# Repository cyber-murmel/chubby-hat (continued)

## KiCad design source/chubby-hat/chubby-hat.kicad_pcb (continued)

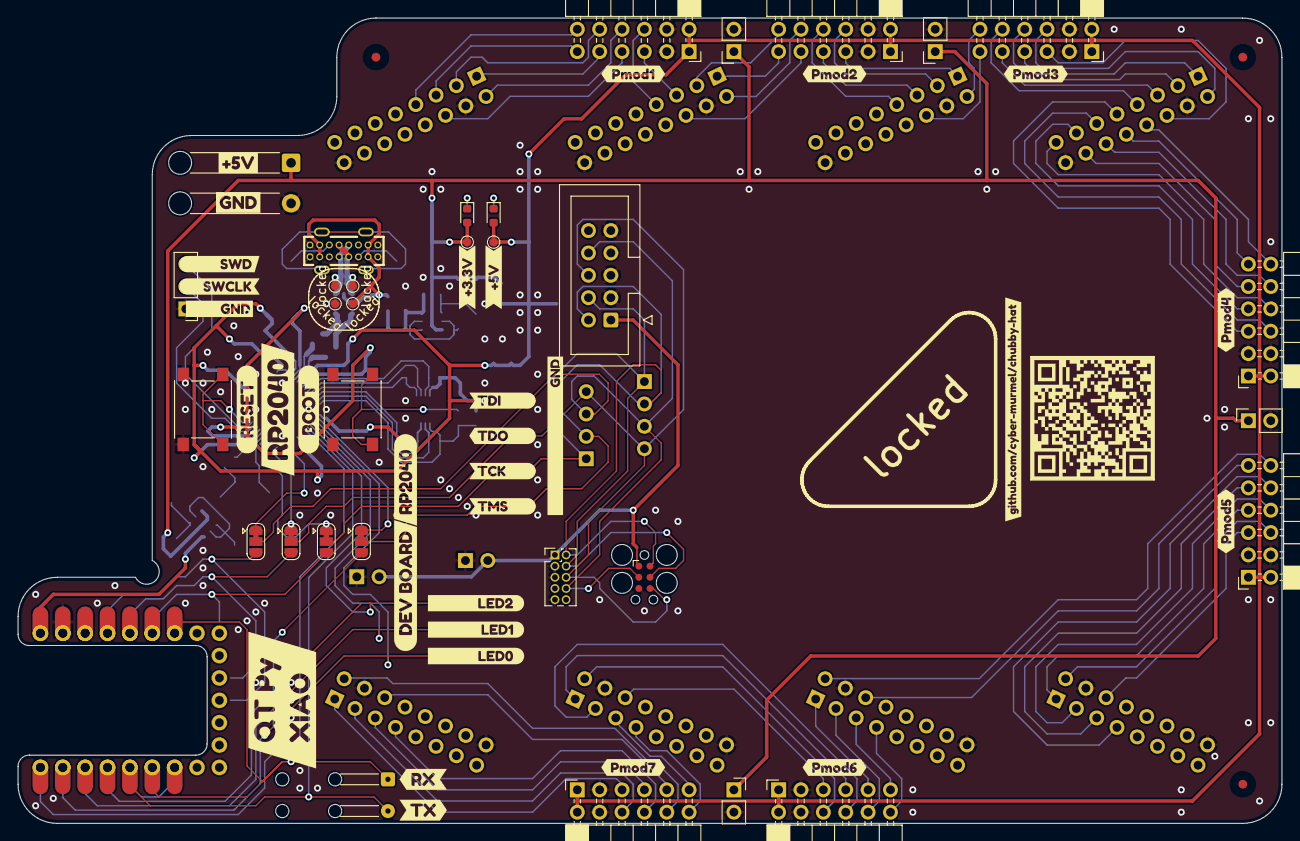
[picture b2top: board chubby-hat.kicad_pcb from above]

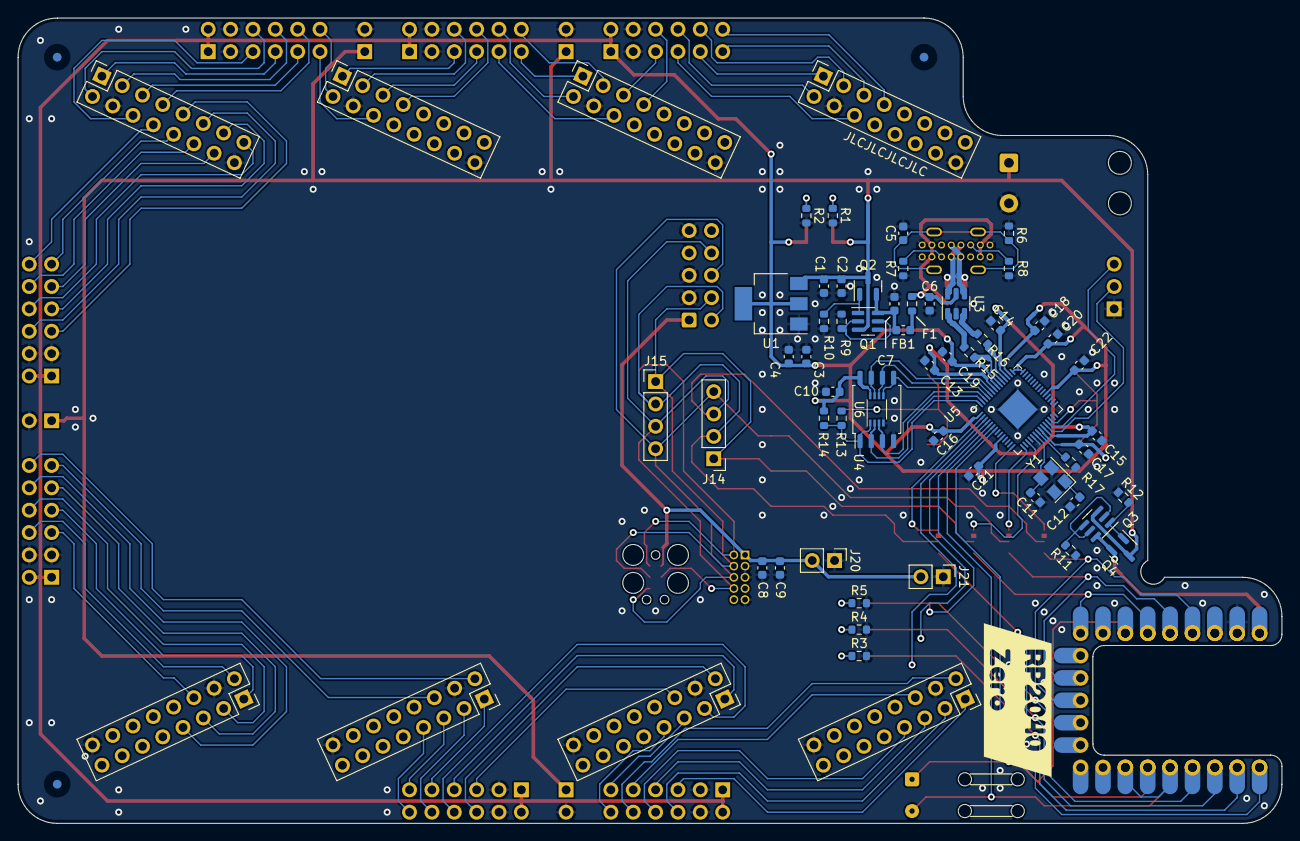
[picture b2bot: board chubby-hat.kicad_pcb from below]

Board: 2 copper layers, 143.5 x 91.4 mm, 143 parts (67 on the bottom side), 115 nets.

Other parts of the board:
QR*****: github.com/cyber-murmel/chubby-hat; github.com_cyber-murmel_chubby-hat
kibuzzard-63D6B6FA: G***; kibuzzard-63D6B6FA
kibuzzard-63D6B15C: G***; kibuzzard-63D6B15C
kibuzzard-63D6B25C: G***; kibuzzard-63D6B25C
kibuzzard-63D6B78A: G***; kibuzzard-63D6B78A
kibuzzard-63D6B79B: G***; kibuzzard-63D6B79B
kibuzzard-63D6B152: G***; kibuzzard-63D6B152
kibuzzard-63D6B171: G***; kibuzzard-63D6B171
kibuzzard-63D6B260: G***; kibuzzard-63D6B260
kibuzzard-63D6CBA0: G***; kibuzzard-63D6CBA0
kibuzzard-63D6CBB9: G***; kibuzzard-63D6CBB9
kibuzzard-63E6D9D7: G***; kibuzzard-63E6D9D7
kibuzzard-63E6D9E4: G***; kibuzzard-63E6D9E4
kibuzzard-63E6D9E9: G***; kibuzzard-63E6D9E9
kibuzzard-63E586AA: G***; kibuzzard-63E586AA
kibuzzard-63E586B9: G***; kibuzzard-63E586B9
kibuzzard-63E586CE: G***; kibuzzard-63E586CE
kibuzzard-63E586D5: G***; kibuzzard-63E586D5
kibuzzard-63E586DD: G***; kibuzzard-63E586DD
kibuzzard-63E586E8: G***; kibuzzard-63E586E8
kibuzzard-63E586F0: G***; kibuzzard-63E586F0
kibuzzard-63E664A0: G***; kibuzzard-63E664A0
kibuzzard-63E664C7: G***; kibuzzard-63E664C7
kibuzzard-63E664D7: G***; kibuzzard-63E664D7
kibuzzard-63E665A8: G***; kibuzzard-63E665A8
kibuzzard-63E665B7: G***; kibuzzard-63E665B7
kibuzzard-63E5252B: G***; kibuzzard-63E5252B
kibuzzard-63E5830C: G***; kibuzzard-63E5830C
kibuzzard-63E5907B: G***; kibuzzard-63E5907B
kibuzzard-63E58302: G***; kibuzzard-63E58302
kibuzzard-63E58321: G***; kibuzzard-63E58321
kibuzzard-63E66495: G***; kibuzzard-63E66495
kibuzzard-63E67724: G***; kibuzzard-63E67724
locked: JP_{TDO}; SolderJumper-3_P1.3mm_Bridged12_RoundedPad1.0x1.5mm
locked#2: JP_{TMS}; SolderJumper-3_P1.3mm_Bridged12_RoundedPad1.0x1.5mm
locked#3: JP_{TDI}; SolderJumper-3_P1.3mm_Bridged12_RoundedPad1.0x1.5mm
locked#4: JP_{TCK}; SolderJumper-3_P1.3mm_Bridged12_RoundedPad1.0x1.5mm

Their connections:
/JTAG.TCK: locked#4.2 (C); also elsewhere on the board
/JTAG.TDI: locked#3.2 (C); also elsewhere on the board
/JTAG.TDO: locked.2 (C); also elsewhere on the board
/JTAG.TMS: locked#2.2 (C); also elsewhere on the board
/JTAG_{DevBoard}.TCK: locked#4.3 (B); also elsewhere on the board
/JTAG_{DevBoard}.TDI: locked#3.3 (B); also elsewhere on the board
/JTAG_{DevBoard}.TDO: locked.3 (B); also elsewhere on the board
/JTAG_{DevBoard}.TMS: locked#2.3 (B); also elsewhere on the board
/RP2040/GPIO0: locked#2.1 (A); also elsewhere on the board
/RP2040/GPIO11: locked#3.1 (A); also elsewhere on the board
/RP2040/GPIO12: locked.1 (A); also elsewhere on the board
/RP2040/GPIO14: locked#4.1 (A); also elsewhere on the board

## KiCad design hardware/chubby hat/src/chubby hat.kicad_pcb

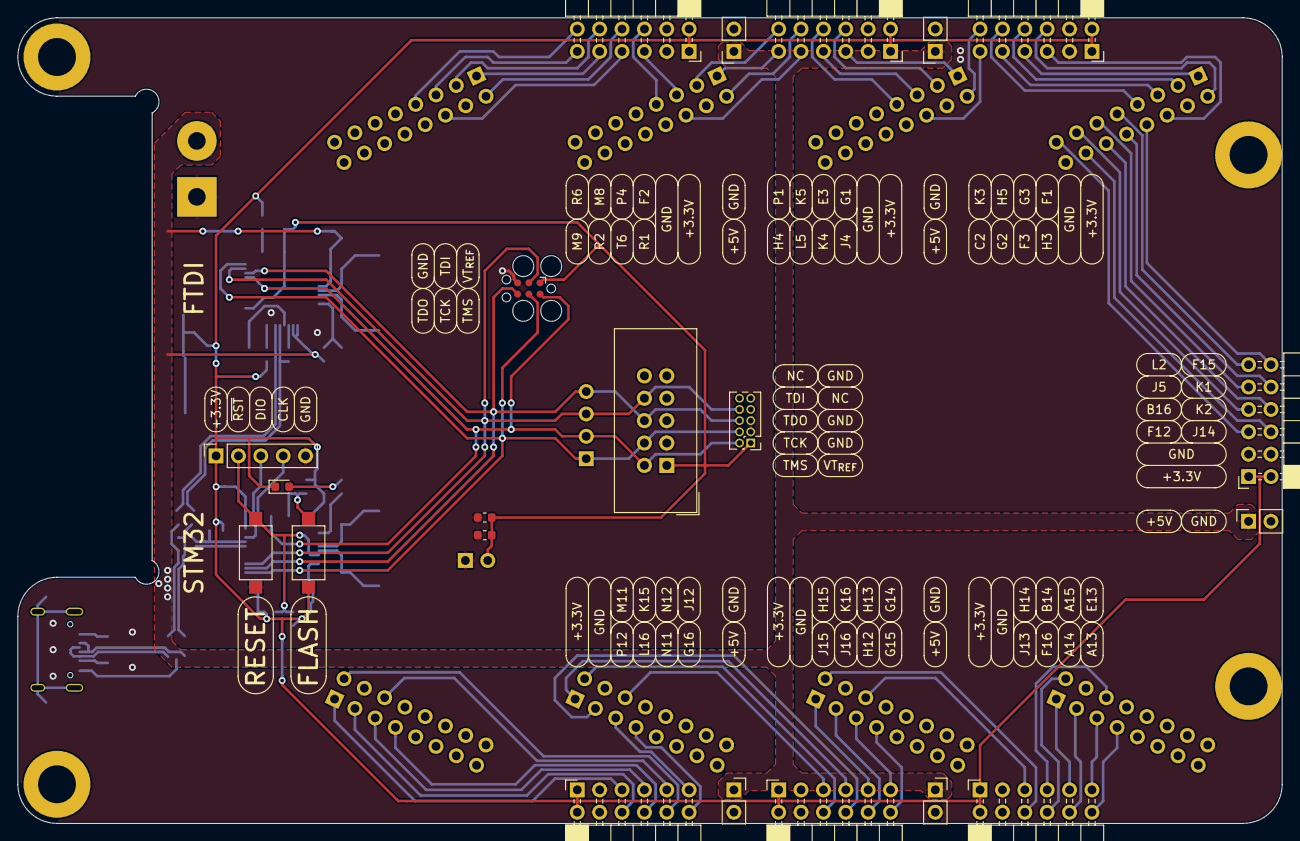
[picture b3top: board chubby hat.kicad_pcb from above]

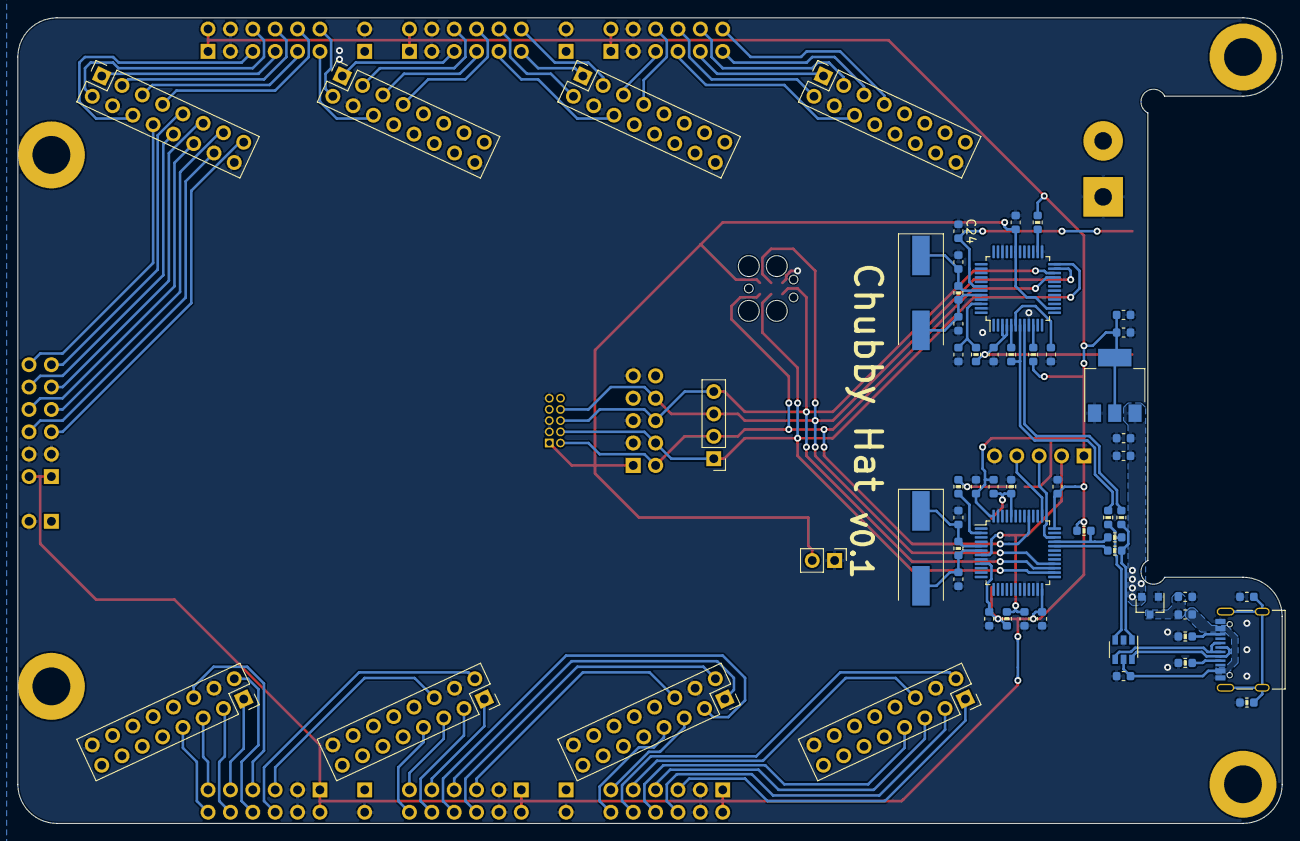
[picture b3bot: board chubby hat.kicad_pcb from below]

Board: 2 copper layers, 143.5 x 91.4 mm, 84 parts (58 on the bottom side), 92 nets.

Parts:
C1, C2, C3, C4, C6, C9, C10, C11, C12, C13, C14, C19, C20, C22, C23, C24: 100n; C_0603_1608Metric_Icon
C5, C7, C8, C21: 1u; C_0603_1608Metric_Icon
C15, C16, C17, C18: 36p; C_0603_1608Metric_Icon
D1: pink; LED_0603_1608Metric
FB1: 600Ω@100MHz; L_0603_1608Metric
H1, H2, H3, H4: M4; MountingHole_4.3mm_M4_ISO7380_Pad
J1, J2, J3, J4, J5, J6, J7, J8: HUB75; PinSocket_2x08_P2.54mm_Vertical
J9: Screw_Terminal_01x02; SolderWirePad_1x02_P7.62mm_Drill2mm
J10: Conn_01x02; PinHeader_1x02_P2.54mm_Vertical
J11: Conn_01x04; PinHeader_1x04_P2.54mm_Vertical
J12: USB_C_Receptacle_USB2.0; USB_C_Receptacle_Palconn_UTC16-G
J13: Conn_ARM_JTAG_SWD_10; IDC-Header_2x05_P2.54mm_Vertical
J14: SWD; PinSocket_1x05_P2.54mm_Vertical
J15, J16, J17, J18, J19: 5V; PinSocket_1x02_P2.54mm_Vertical
J20: Conn_ARM_JTAG_SWD_10; PinHeader_2x05_P1.27mm_Vertical
J21: TC2030; Tag-Connect_TC2030-IDC-FP_2x03_P1.27mm_Vertical
Pmod1, Pmod2, Pmod3, Pmod4, Pmod5, Pmod6, Pmod7: Pmod_02x06_Host; PinSocket_2x06_P2.54mm_Horizontal
Q1: AO3401A; SOT-23
R1, R2: 27; R_0603_1608Metric_Icon
R3, R8, R9: 1M; R_0603_1608Metric_Icon
R6, R7: 20; R_0603_1608Metric_Icon
R10, R11: 5.1k; R_0603_1608Metric_Icon
R12, R16, R19, R20: 1.5k; R_0603_1608Metric_Icon
R13, R15, R17: 10k; R_0603_1608Metric_Icon
R18: 470; R_0603_1608Metric_Icon
SW2: reset; SW_SPST_CK_RS282G05A3
SW3: boot0; SW_SPST_CK_RS282G05A3
U1: FT2232D; LQFP-48_7x7mm_P0.5mm
U2: USBLC6-2SC6; SOT-23-6
U3: STM32F103C8Tx; LQFP-48_7x7mm_P0.5mm
U4: AMS1117-3.3; SOT-223-3_TabPin2
Y1: 6MHz; Crystal_SMD_HC49-SD
Y2: 8MHz; Crystal_SMD_HC49-SD

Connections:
+3V3: C8.2, C9.2, C10.2, C11.2, C12.2, C13.2, C23.1, D1.1 (K), J14.1, Pmod1.1 (VCC), Pmod1.2 (VCC), Pmod2.1 (VCC), Pmod2.2 (VCC), Pmod3.1 (VCC), Pmod3.2 (VCC), Pmod4.1 (VCC), Pmod4.2 (VCC), Pmod5.1 (VCC), Pmod5.2 (VCC), Pmod6.1 (VCC), Pmod6.2 (VCC), Pmod7.1 (VCC), Pmod7.2 (VCC), R12.2, R13.2, R19.1, R20.1, SW3.1, U3.9 (VDDA), U3.24 (VDD), U3.36 (VDD), U3.48 (VDD), U4.2 (VO)
+5V: C6.2, C7.2, C20.2, C24.2, J9.2, J15.1, J16.1, J17.1, J18.1, J19.1, Q1.2 (S), R18.2, U1.3 (VCC), U1.4 (~RESET), U1.42 (VCC), U4.3 (VI)
/Blue Pill/BOOT0: C23.2, R15.1, SW3.2, U3.44 (BOOT0)
/Blue Pill/D_N: R7.2, U3.32 (PA11)
/Blue Pill/D_P: R6.1, R12.1, U3.33 (PA12)
/Blue Pill/OSCIN: C15.2, R3.1, U3.5 (PD0), Y2.1
/Blue Pill/OSCOUT: C16.2, R3.2, U3.6 (PD1), Y2.2
/Blue Pill/STM32_~RESET~: C14.2, J14.2, R13.1, SW2.2, U3.7 (NRST)
/Blue Pill/SWCLK: J14.4, U3.37 (PA14)
/Blue Pill/SWDIO: J14.3, U3.34 (PA13)
/FTDI/D_N: R1.1, U1.8 (USBDM)
/FTDI/D_P: R2.2, R16.2, U1.7 (USBDP)
/JTAG.TCK: J11.1, J13.4 (SWDCLK/TCK), J20.4 (SWDCLK/TCK), J21.4, U1.24 (ADBUS0), U3.26 (PB13)
/JTAG.TDI: J11.3, J13.8 (NC/TDI), J20.8 (NC/TDI), J21.3, U1.23 (ADBUS1), U3.28 (PB15)
/JTAG.TDO: J11.4, J13.6 (SWO/TDO), J20.6 (SWO/TDO), J21.6, U1.22 (ADBUS2), U3.27 (PB14)
/JTAG.TMS: J11.2, J13.2 (SWDIO/TMS), J20.2 (SWDIO/TMS), J21.2, U1.21 (ADBUS3), U3.40 (PB4)
/Pmod1_IO1: J1.9, Pmod1.11 (IO1)
/Pmod1_IO2: J1.11, Pmod1.9 (IO2)
/Pmod1_IO3: J1.13, Pmod1.7 (IO3)
/Pmod1_IO4: J1.15, Pmod1.5 (IO4)
/Pmod1_IO5: J1.8, Pmod1.12 (IO5)
/Pmod1_IO6: J1.10, Pmod1.10 (IO6)
/Pmod1_IO7: J1.12, Pmod1.8 (IO7)
/Pmod1_IO8: J1.14, Pmod1.6 (IO8)
/Pmod2_IO1: J2.6, Pmod2.11 (IO1)
/Pmod2_IO2: J1.5, Pmod2.9 (IO2)
/Pmod2_IO3: J1.1, Pmod2.7 (IO3)
/Pmod2_IO4: J1.6, Pmod2.5 (IO4)
/Pmod2_IO5: J2.2, Pmod2.12 (IO5)
/Pmod2_IO6: J1.7, Pmod2.10 (IO6)
/Pmod2_IO7: J1.3, Pmod2.8 (IO7)
/Pmod2_IO8: J1.2, Pmod2.6 (IO8)
/Pmod3_IO1: J3.1, Pmod3.11 (IO1)
/Pmod3_IO2: J3.6, Pmod3.9 (IO2)
/Pmod3_IO3: J2.5, Pmod3.7 (IO3)
/Pmod3_IO4: J2.1, Pmod3.5 (IO4)
/Pmod3_IO5: J3.3, Pmod3.12 (IO5)
/Pmod3_IO6: J3.2, Pmod3.10 (IO6)
/Pmod3_IO7: J2.7, Pmod3.8 (IO7)
/Pmod3_IO8: J2.3, Pmod3.6 (IO8)
/Pmod4_IO1: J4.5, Pmod4.11 (IO1)
/Pmod4_IO2: J4.1, Pmod4.9 (IO2)
/Pmod4_IO3: J4.6, Pmod4.7 (IO3)
/Pmod4_IO4: J3.5, Pmod4.5 (IO4)
/Pmod4_IO5: J4.7, Pmod4.12 (IO5)
/Pmod4_IO6: J4.3, Pmod4.10 (IO6)
/Pmod4_IO7: J4.2, Pmod4.8 (IO7)
/Pmod4_IO8: J3.7, Pmod4.6 (IO8)
/Pmod5_IO1: J6.5, Pmod5.11 (IO1)
/Pmod5_IO2: J5.6, Pmod5.9 (IO2)
/Pmod5_IO3: J5.5, Pmod5.7 (IO3)
/Pmod5_IO4: J5.1, Pmod5.5 (IO4)
/Pmod5_IO5: J6.7, Pmod5.12 (IO5)
/Pmod5_IO6: J5.2, Pmod5.10 (IO6)
/Pmod5_IO7: J5.7, Pmod5.8 (IO7)
/Pmod5_IO8: J5.3, Pmod5.6 (IO8)
/Pmod6_IO1: J7.5, Pmod6.11 (IO1)
/Pmod6_IO2: J7.1, Pmod6.9 (IO2)
/Pmod6_IO3: J6.1, Pmod6.7 (IO3)
/Pmod6_IO4: J6.6, Pmod6.5 (IO4)
/Pmod6_IO5: J7.7, Pmod6.12 (IO5)
/Pmod6_IO6: J7.3, Pmod6.10 (IO6)
/Pmod6_IO7: J6.3, Pmod6.8 (IO7)
/Pmod6_IO8: J6.2, Pmod6.6 (IO8)
/Pmod7_IO1: J8.5, Pmod7.11 (IO1)
/Pmod7_IO2: J8.1, Pmod7.9 (IO2)
/Pmod7_IO3: J8.6, Pmod7.7 (IO3)
/Pmod7_IO4: J7.6, Pmod7.5 (IO4)
/Pmod7_IO5: J8.7, Pmod7.12 (IO5)
/Pmod7_IO6: J8.3, Pmod7.10 (IO6)
/Pmod7_IO7: J8.2, Pmod7.8 (IO7)
/Pmod7_IO8: J7.2, Pmod7.6 (IO8)
/Type C USB 2.0/D_N: J12.A7 (D-), J12.B7 (D-), U2.6 (IO1)
/Type C USB 2.0/D_P: J12.A6 (D+), J12.B6 (D+), U2.4 (IO2)
/USB.D+: R2.1, R6.2, U2.3 (IO2)
/USB.D-: R1.2, R7.1, U2.1 (IO1)
Earth: C3.1, J12.S1 (SHIELD), R9.2
GND: C1.2, C2.2, C3.2, C4.1, C5.1, C6.1, C7.1, C8.1, C9.1, C10.1, C11.1, C12.1, C13.1, C14.1, C15.1, C16.1, C17.1, C18.1, C19.1, C20.1, C21.1, C22.1, C24.1, J1.4, J1.16, J2.4, J2.16, J3.4, J3.16, J4.4, J4.16, J5.4, J5.16, J6.4, J6.16, J7.4, J7.16, J8.4, J8.16, J9.1, J10.1, J12.A1 (GND), J12.A12 (GND), J12.B1 (GND), J12.B12 (GND), J13.3 (GND), J13.5 (GND), J13.9 (GNDDetect), J14.5, J15.2, J16.2, J17.2, J18.2, J19.2, J20.3 (GND), J20.5 (GND), J20.9 (GNDDetect), J21.5, Pmod1.3 (GND), Pmod1.4 (GND), Pmod2.3 (GND), Pmod2.4 (GND), Pmod3.3 (GND), Pmod3.4 (GND), Pmod4.3 (GND), Pmod4.4 (GND), Pmod5.3 (GND), Pmod5.4 (GND), Pmod6.3 (GND), Pmod6.4 (GND), Pmod7.3 (GND), Pmod7.4 (GND), Q1.1 (G), R9.1, R10.1, R11.1, R15.2, SW2.1, U1.9 (GND), U1.18 (GND), U1.25 (GND), U1.34 (GND), U1.45 (AGND), U1.47 (TEST), U2.2 (GND), U3.8 (VSSA), U3.20 (PB2), U3.23 (VSS), U3.35 (VSS), U3.47 (VSS), U4.1 (GND)
unnamed: C2.1, U1.6 (3V3OUT)
unnamed: C5.2, FB1.1, Q1.3 (D)
unnamed: C17.2, R8.1, U1.43 (XTIN), Y1.1
unnamed: C18.2, R8.2, U1.44 (XTOUT), Y1.2
unnamed: C19.2, R18.1, U1.46 (AVCC)
unnamed: D1.2 (A), R17.2
unnamed: J12.A5 (CC1), R10.2
unnamed: J12.B5 (CC2), R11.2
unnamed: R16.1, U1.5 (~RSTOUT)
unnamed: R17.1, U3.2 (PC13)
unnamed: R19.2, U1.10 (SI/WUA)
unnamed: R20.2, U1.26 (SI/WUB)
VBUS: C4.2, FB1.2, J12.A4 (VBUS), J12.A9 (VBUS), J12.B4 (VBUS), J12.B9 (VBUS), U2.5 (VBUS)
VDD: C1.1, C21.2, C22.2, J10.2, J13.1 (VTref), J20.1 (VTref), J21.1, U1.14 (VCCIOA), U1.31 (VCCIOB)

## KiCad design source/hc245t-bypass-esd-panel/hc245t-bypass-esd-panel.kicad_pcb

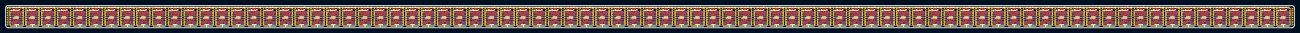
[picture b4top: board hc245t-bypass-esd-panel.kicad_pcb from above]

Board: 2 copper layers, 466.0 x 8.0 mm, 405 parts (0 on the bottom side), 11 nets.

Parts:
C1, C2, C3, C4, C5, C6, C7, C8, C9, C10, C11, C12, C13, C14, C15, C16, C17, C18, C19, C20, C21, C22, C23, C24, C25, C26, C27, C28, C29, C30, C31, C32, C33, C34, C35, C36, C37, C38, C39, C40, C41, C42, C43, C44, C45, C46, C47, C48, C49, C50, C51, C52, C53, C54, C55, C56, C57, C58, C59, C60, C61, C62, C63, C64, C65, C66, C67, C68, C69, C70, C71, C72, C73, C74, C75, C76, C77, C78, C79, C80, C81: C; C_0402_1005Metric
R1, R2, R3, R4, R5, R6, R7, R8, R9, R10, R11, R12, R13, R14, R15, R16, R17, R18, R19, R20, R21, R22, R23, R24, R25, R26, R27, R28, R29, R30, R31, R32, R33, R34, R35, R36, R37, R38, R39, R40, R41, R42, R43, R44, R45, R46, R47, R48, R49, R50, R51, R52, R53, R54, R55, R56, R57, R58, R59, R60, R61, R62, R63, R64, R65, R66, R67, R68, R69, R70, R71, R72, R73, R74, R75, R76, R77, R78, R79, R80, R81: R; R_0402_1005Metric
U1, U4, U7, U10, U13, U16, U19, U22, U25, U28, U31, U34, U37, U40, U43, U46, U49, U52, U55, U58, U61, U64, U67, U70, U73, U76, U79, U82, U85, U88, U91, U94, U97, U100, U103, U106, U109, U112, U115, U118, U121, U124, U127, U130, U133, U136, U139, U142, U145, U148, U151, U154, U157, U160, U163, U166, U169, U172, U175, U178, U181, U184, U187, U190, U193, U196, U199, U202, U205, U208, U211, U214, U217, U220, U223, U226, U229, U232, U235, U238, U241: 74HC245; TSSOP-20_4.4x6.5mm_P0.65mm
U2, U3, U5, U6, U8, U9, U11, U12, U14, U15, U17, U18, U20, U21, U23, U24, U26, U27, U29, U30, U32, U33, U35, U36, U38, U39, U41, U42, U44, U45, U47, U48, U50, U51, U53, U54, U56, U57, U59, U60, U62, U63, U65, U66, U68, U69, U71, U72, U74, U75, U77, U78, U80, U81, U83, U84, U86, U87, U89, U90, U92, U93, U95, U96, U98, U99, U101, U102, U104, U105, U107, U108, U110, U111, U113, U114, U116, U117, U119, U120, U122, U123, U125, U126, U128, U129, U131, U132, U134, U135, U137, U138, U140, U141, U143, U144, U146, U147, U149, U150, U152, U153, U155, U156, U158, U159, U161, U162, U164, U165, U167, U168, U170, U171, U173, U174, U176, U177, U179, U180, U182, U183, U185, U186, U188, U189, U191, U192, U194, U195, U197, U198, U200, U201, U203, U204, U206, U207, U209, U210, U212, U213, U215, U216, U218, U219, U221, U222, U224, U225, U227, U228, U230, U231, U233, U234, U236, U237, U239, U240, U242, U243: NUP4202; SOT-363_SC-70-6

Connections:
/D0: U1.2 (A0), U1.18 (B0), U2.6, U4.2 (A0), U4.18 (B0), U5.6, U7.2 (A0), U7.18 (B0), U8.6, U10.2 (A0), U10.18 (B0), U11.6, U13.2 (A0), U13.18 (B0), U14.6, U16.2 (A0), U16.18 (B0), U17.6, U19.2 (A0), U19.18 (B0), U20.6, U22.2 (A0), U22.18 (B0), U23.6, U25.2 (A0), U25.18 (B0), U26.6, U28.2 (A0), U28.18 (B0), U29.6, U31.2 (A0), U31.18 (B0), U32.6, U34.2 (A0), U34.18 (B0), U35.6, U37.2 (A0), U37.18 (B0), U38.6, U40.2 (A0), U40.18 (B0), U41.6, U43.2 (A0), U43.18 (B0), U44.6, U46.2 (A0), U46.18 (B0), U47.6, U49.2 (A0), U49.18 (B0), U50.6, U52.2 (A0), U52.18 (B0), U53.6, U55.2 (A0), U55.18 (B0), U56.6, U58.2 (A0), U58.18 (B0), U59.6, U61.2 (A0), U61.18 (B0), U62.6, U64.2 (A0), U64.18 (B0), U65.6, U67.2 (A0), U67.18 (B0), U68.6, U70.2 (A0), U70.18 (B0), U71.6, U73.2 (A0), U73.18 (B0), U74.6, U76.2 (A0), U76.18 (B0), U77.6, U79.2 (A0), U79.18 (B0), U80.6, U82.2 (A0), U82.18 (B0), U83.6, U85.2 (A0), U85.18 (B0), U86.6, U88.2 (A0), U88.18 (B0), U89.6, U91.2 (A0), U91.18 (B0), U92.6, U94.2 (A0), U94.18 (B0), U95.6, U97.2 (A0), U97.18 (B0), U98.6, U100.2 (A0), U100.18 (B0), U101.6, U103.2 (A0), U103.18 (B0), U104.6, U106.2 (A0), U106.18 (B0), U107.6, U109.2 (A0), U109.18 (B0), U110.6, U112.2 (A0), U112.18 (B0), U113.6, U115.2 (A0), U115.18 (B0), U116.6, U118.2 (A0), U118.18 (B0), U119.6, U121.2 (A0), U121.18 (B0), U122.6, U124.2 (A0), U124.18 (B0), U125.6, U127.2 (A0), U127.18 (B0), U128.6, U130.2 (A0), U130.18 (B0), U131.6, U133.2 (A0), U133.18 (B0), U134.6, U136.2 (A0), U136.18 (B0), U137.6, U139.2 (A0), U139.18 (B0), U140.6, U142.2 (A0), U142.18 (B0), U143.6, U145.2 (A0), U145.18 (B0), U146.6, U148.2 (A0), U148.18 (B0), U149.6, U151.2 (A0), U151.18 (B0), U152.6, U154.2 (A0), U154.18 (B0), U155.6, U157.2 (A0), U157.18 (B0), U158.6, U160.2 (A0), U160.18 (B0), U161.6, U163.2 (A0), U163.18 (B0), U164.6, U166.2 (A0), U166.18 (B0), U167.6, U169.2 (A0), U169.18 (B0), U170.6, U172.2 (A0), U172.18 (B0), U173.6, U175.2 (A0), U175.18 (B0), U176.6, U178.2 (A0), U178.18 (B0), U179.6, U181.2 (A0), U181.18 (B0), U182.6, U184.2 (A0), U184.18 (B0), U185.6, U187.2 (A0), U187.18 (B0), U188.6, U190.2 (A0)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
/D1: U1.3 (A1), U1.17 (B1), U2.1, U4.3 (A1), U4.17 (B1), U5.1, U7.3 (A1), U7.17 (B1), U8.1, U10.3 (A1), U10.17 (B1), U11.1, U13.3 (A1), U13.17 (B1), U14.1, U16.3 (A1), U16.17 (B1), U17.1, U19.3 (A1), U19.17 (B1), U20.1, U22.3 (A1), U22.17 (B1), U23.1, U25.3 (A1), U25.17 (B1), U26.1, U28.3 (A1), U28.17 (B1), U29.1, U31.3 (A1), U31.17 (B1), U32.1, U34.3 (A1), U34.17 (B1), U35.1, U37.3 (A1), U37.17 (B1), U38.1, U40.3 (A1), U40.17 (B1), U41.1, U43.3 (A1), U43.17 (B1), U44.1, U46.3 (A1), U46.17 (B1), U47.1, U49.3 (A1), U49.17 (B1), U50.1, U52.3 (A1), U52.17 (B1), U53.1, U55.3 (A1), U55.17 (B1), U56.1, U58.3 (A1), U58.17 (B1), U59.1, U61.3 (A1), U61.17 (B1), U62.1, U64.3 (A1), U64.17 (B1), U65.1, U67.3 (A1), U67.17 (B1), U68.1, U70.3 (A1), U70.17 (B1), U71.1, U73.3 (A1), U73.17 (B1), U74.1, U76.3 (A1), U76.17 (B1), U77.1, U79.3 (A1), U79.17 (B1), U80.1, U82.3 (A1), U82.17 (B1), U83.1, U85.3 (A1), U85.17 (B1), U86.1, U88.3 (A1), U88.17 (B1), U89.1, U91.3 (A1), U91.17 (B1), U92.1, U94.3 (A1), U94.17 (B1), U95.1, U97.3 (A1), U97.17 (B1), U98.1, U100.3 (A1), U100.17 (B1), U101.1, U103.3 (A1), U103.17 (B1), U104.1, U106.3 (A1), U106.17 (B1), U107.1, U109.3 (A1), U109.17 (B1), U110.1, U112.3 (A1), U112.17 (B1), U113.1, U115.3 (A1), U115.17 (B1), U116.1, U118.3 (A1), U118.17 (B1), U119.1, U121.3 (A1), U121.17 (B1), U122.1, U124.3 (A1), U124.17 (B1), U125.1, U127.3 (A1), U127.17 (B1), U128.1, U130.3 (A1), U130.17 (B1), U131.1, U133.3 (A1), U133.17 (B1), U134.1, U136.3 (A1), U136.17 (B1), U137.1, U139.3 (A1), U139.17 (B1), U140.1, U142.3 (A1), U142.17 (B1), U143.1, U145.3 (A1), U145.17 (B1), U146.1, U148.3 (A1), U148.17 (B1), U149.1, U151.3 (A1), U151.17 (B1), U152.1, U154.3 (A1), U154.17 (B1), U155.1, U157.3 (A1), U157.17 (B1), U158.1, U160.3 (A1), U160.17 (B1), U161.1, U163.3 (A1), U163.17 (B1), U164.1, U166.3 (A1), U166.17 (B1), U167.1, U169.3 (A1), U169.17 (B1), U170.1, U172.3 (A1), U172.17 (B1), U173.1, U175.3 (A1), U175.17 (B1), U176.1, U178.3 (A1), U178.17 (B1), U179.1, U181.3 (A1), U181.17 (B1), U182.1, U184.3 (A1), U184.17 (B1), U185.1, U187.3 (A1), U187.17 (B1), U188.1, U190.3 (A1)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
/D2: U1.4 (A2), U1.16 (B2), U2.4, U4.4 (A2), U4.16 (B2), U5.4, U7.4 (A2), U7.16 (B2), U8.4, U10.4 (A2), U10.16 (B2), U11.4, U13.4 (A2), U13.16 (B2), U14.4, U16.4 (A2), U16.16 (B2), U17.4, U19.4 (A2), U19.16 (B2), U20.4, U22.4 (A2), U22.16 (B2), U23.4, U25.4 (A2), U25.16 (B2), U26.4, U28.4 (A2), U28.16 (B2), U29.4, U31.4 (A2), U31.16 (B2), U32.4, U34.4 (A2), U34.16 (B2), U35.4, U37.4 (A2), U37.16 (B2), U38.4, U40.4 (A2), U40.16 (B2), U41.4, U43.4 (A2), U43.16 (B2), U44.4, U46.4 (A2), U46.16 (B2), U47.4, U49.4 (A2), U49.16 (B2), U50.4, U52.4 (A2), U52.16 (B2), U53.4, U55.4 (A2), U55.16 (B2), U56.4, U58.4 (A2), U58.16 (B2), U59.4, U61.4 (A2), U61.16 (B2), U62.4, U64.4 (A2), U64.16 (B2), U65.4, U67.4 (A2), U67.16 (B2), U68.4, U70.4 (A2), U70.16 (B2), U71.4, U73.4 (A2), U73.16 (B2), U74.4, U76.4 (A2), U76.16 (B2), U77.4, U79.4 (A2), U79.16 (B2), U80.4, U82.4 (A2), U82.16 (B2), U83.4, U85.4 (A2), U85.16 (B2), U86.4, U88.4 (A2), U88.16 (B2), U89.4, U91.4 (A2), U91.16 (B2), U92.4, U94.4 (A2), U94.16 (B2), U95.4, U97.4 (A2), U97.16 (B2), U98.4, U100.4 (A2), U100.16 (B2), U101.4, U103.4 (A2), U103.16 (B2), U104.4, U106.4 (A2), U106.16 (B2), U107.4, U109.4 (A2), U109.16 (B2), U110.4, U112.4 (A2), U112.16 (B2), U113.4, U115.4 (A2), U115.16 (B2), U116.4, U118.4 (A2), U118.16 (B2), U119.4, U121.4 (A2), U121.16 (B2), U122.4, U124.4 (A2), U124.16 (B2), U125.4, U127.4 (A2), U127.16 (B2), U128.4, U130.4 (A2), U130.16 (B2), U131.4, U133.4 (A2), U133.16 (B2), U134.4, U136.4 (A2), U136.16 (B2), U137.4, U139.4 (A2), U139.16 (B2), U140.4, U142.4 (A2), U142.16 (B2), U143.4, U145.4 (A2), U145.16 (B2), U146.4, U148.4 (A2), U148.16 (B2), U149.4, U151.4 (A2), U151.16 (B2), U152.4, U154.4 (A2), U154.16 (B2), U155.4, U157.4 (A2), U157.16 (B2), U158.4, U160.4 (A2), U160.16 (B2), U161.4, U163.4 (A2), U163.16 (B2), U164.4, U166.4 (A2), U166.16 (B2), U167.4, U169.4 (A2), U169.16 (B2), U170.4, U172.4 (A2), U172.16 (B2), U173.4, U175.4 (A2), U175.16 (B2), U176.4, U178.4 (A2), U178.16 (B2), U179.4, U181.4 (A2), U181.16 (B2), U182.4, U184.4 (A2), U184.16 (B2), U185.4, U187.4 (A2), U187.16 (B2), U188.4, U190.4 (A2)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
/D3: U1.5 (A3), U1.15 (B3), U2.3, U4.5 (A3), U4.15 (B3), U5.3, U7.5 (A3), U7.15 (B3), U8.3, U10.5 (A3), U10.15 (B3), U11.3, U13.5 (A3), U13.15 (B3), U14.3, U16.5 (A3), U16.15 (B3), U17.3, U19.5 (A3), U19.15 (B3), U20.3, U22.5 (A3), U22.15 (B3), U23.3, U25.5 (A3), U25.15 (B3), U26.3, U28.5 (A3), U28.15 (B3), U29.3, U31.5 (A3), U31.15 (B3), U32.3, U34.5 (A3), U34.15 (B3), U35.3, U37.5 (A3), U37.15 (B3), U38.3, U40.5 (A3), U40.15 (B3), U41.3, U43.5 (A3), U43.15 (B3), U44.3, U46.5 (A3), U46.15 (B3), U47.3, U49.5 (A3), U49.15 (B3), U50.3, U52.5 (A3), U52.15 (B3), U53.3, U55.5 (A3), U55.15 (B3), U56.3, U58.5 (A3), U58.15 (B3), U59.3, U61.5 (A3), U61.15 (B3), U62.3, U64.5 (A3), U64.15 (B3), U65.3, U67.5 (A3), U67.15 (B3), U68.3, U70.5 (A3), U70.15 (B3), U71.3, U73.5 (A3), U73.15 (B3), U74.3, U76.5 (A3), U76.15 (B3), U77.3, U79.5 (A3), U79.15 (B3), U80.3, U82.5 (A3), U82.15 (B3), U83.3, U85.5 (A3), U85.15 (B3), U86.3, U88.5 (A3), U88.15 (B3), U89.3, U91.5 (A3), U91.15 (B3), U92.3, U94.5 (A3), U94.15 (B3), U95.3, U97.5 (A3), U97.15 (B3), U98.3, U100.5 (A3), U100.15 (B3), U101.3, U103.5 (A3), U103.15 (B3), U104.3, U106.5 (A3), U106.15 (B3), U107.3, U109.5 (A3), U109.15 (B3), U110.3, U112.5 (A3), U112.15 (B3), U113.3, U115.5 (A3), U115.15 (B3), U116.3, U118.5 (A3), U118.15 (B3), U119.3, U121.5 (A3), U121.15 (B3), U122.3, U124.5 (A3), U124.15 (B3), U125.3, U127.5 (A3), U127.15 (B3), U128.3, U130.5 (A3), U130.15 (B3), U131.3, U133.5 (A3), U133.15 (B3), U134.3, U136.5 (A3), U136.15 (B3), U137.3, U139.5 (A3), U139.15 (B3), U140.3, U142.5 (A3), U142.15 (B3), U143.3, U145.5 (A3), U145.15 (B3), U146.3, U148.5 (A3), U148.15 (B3), U149.3, U151.5 (A3), U151.15 (B3), U152.3, U154.5 (A3), U154.15 (B3), U155.3, U157.5 (A3), U157.15 (B3), U158.3, U160.5 (A3), U160.15 (B3), U161.3, U163.5 (A3), U163.15 (B3), U164.3, U166.5 (A3), U166.15 (B3), U167.3, U169.5 (A3), U169.15 (B3), U170.3, U172.5 (A3), U172.15 (B3), U173.3, U175.5 (A3), U175.15 (B3), U176.3, U178.5 (A3), U178.15 (B3), U179.3, U181.5 (A3), U181.15 (B3), U182.3, U184.5 (A3), U184.15 (B3), U185.3, U187.5 (A3), U187.15 (B3), U188.3, U190.5 (A3)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
/D4: U1.6 (A4), U1.14 (B4), U3.6, U4.6 (A4), U4.14 (B4), U6.6, U7.6 (A4), U7.14 (B4), U9.6, U10.6 (A4), U10.14 (B4), U12.6, U13.6 (A4), U13.14 (B4), U15.6, U16.6 (A4), U16.14 (B4), U18.6, U19.6 (A4), U19.14 (B4), U21.6, U22.6 (A4), U22.14 (B4), U24.6, U25.6 (A4), U25.14 (B4), U27.6, U28.6 (A4), U28.14 (B4), U30.6, U31.6 (A4), U31.14 (B4), U33.6, U34.6 (A4), U34.14 (B4), U36.6, U37.6 (A4), U37.14 (B4), U39.6, U40.6 (A4), U40.14 (B4), U42.6, U43.6 (A4), U43.14 (B4), U45.6, U46.6 (A4), U46.14 (B4), U48.6, U49.6 (A4), U49.14 (B4), U51.6, U52.6 (A4), U52.14 (B4), U54.6, U55.6 (A4), U55.14 (B4), U57.6, U58.6 (A4), U58.14 (B4), U60.6, U61.6 (A4), U61.14 (B4), U63.6, U64.6 (A4), U64.14 (B4), U66.6, U67.6 (A4), U67.14 (B4), U69.6, U70.6 (A4), U70.14 (B4), U72.6, U73.6 (A4), U73.14 (B4), U75.6, U76.6 (A4), U76.14 (B4), U78.6, U79.6 (A4), U79.14 (B4), U81.6, U82.6 (A4), U82.14 (B4), U84.6, U85.6 (A4), U85.14 (B4), U87.6, U88.6 (A4), U88.14 (B4), U90.6, U91.6 (A4), U91.14 (B4), U93.6, U94.6 (A4), U94.14 (B4), U96.6, U97.6 (A4), U97.14 (B4), U99.6, U100.6 (A4), U100.14 (B4), U102.6, U103.6 (A4), U103.14 (B4), U105.6, U106.6 (A4), U106.14 (B4), U108.6, U109.6 (A4), U109.14 (B4), U111.6, U112.6 (A4), U112.14 (B4), U114.6, U115.6 (A4), U115.14 (B4), U117.6, U118.6 (A4), U118.14 (B4), U120.6, U121.6 (A4), U121.14 (B4), U123.6, U124.6 (A4), U124.14 (B4), U126.6, U127.6 (A4), U127.14 (B4), U129.6, U130.6 (A4), U130.14 (B4), U132.6, U133.6 (A4), U133.14 (B4), U135.6, U136.6 (A4), U136.14 (B4), U138.6, U139.6 (A4), U139.14 (B4), U141.6, U142.6 (A4), U142.14 (B4), U144.6, U145.6 (A4), U145.14 (B4), U147.6, U148.6 (A4), U148.14 (B4), U150.6, U151.6 (A4), U151.14 (B4), U153.6, U154.6 (A4), U154.14 (B4), U156.6, U157.6 (A4), U157.14 (B4), U159.6, U160.6 (A4), U160.14 (B4), U162.6, U163.6 (A4), U163.14 (B4), U165.6, U166.6 (A4), U166.14 (B4), U168.6, U169.6 (A4), U169.14 (B4), U171.6, U172.6 (A4), U172.14 (B4), U174.6, U175.6 (A4), U175.14 (B4), U177.6, U178.6 (A4), U178.14 (B4), U180.6, U181.6 (A4), U181.14 (B4), U183.6, U184.6 (A4), U184.14 (B4), U186.6, U187.6 (A4), U187.14 (B4), U189.6, U190.6 (A4)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
/D5: U1.7 (A5), U1.13 (B5), U3.1, U4.7 (A5), U4.13 (B5), U6.1, U7.7 (A5), U7.13 (B5), U9.1, U10.7 (A5), U10.13 (B5), U12.1, U13.7 (A5), U13.13 (B5), U15.1, U16.7 (A5), U16.13 (B5), U18.1, U19.7 (A5), U19.13 (B5), U21.1, U22.7 (A5), U22.13 (B5), U24.1, U25.7 (A5), U25.13 (B5), U27.1, U28.7 (A5), U28.13 (B5), U30.1, U31.7 (A5), U31.13 (B5), U33.1, U34.7 (A5), U34.13 (B5), U36.1, U37.7 (A5), U37.13 (B5), U39.1, U40.7 (A5), U40.13 (B5), U42.1, U43.7 (A5), U43.13 (B5), U45.1, U46.7 (A5), U46.13 (B5), U48.1, U49.7 (A5), U49.13 (B5), U51.1, U52.7 (A5), U52.13 (B5), U54.1, U55.7 (A5), U55.13 (B5), U57.1, U58.7 (A5), U58.13 (B5), U60.1, U61.7 (A5), U61.13 (B5), U63.1, U64.7 (A5), U64.13 (B5), U66.1, U67.7 (A5), U67.13 (B5), U69.1, U70.7 (A5), U70.13 (B5), U72.1, U73.7 (A5), U73.13 (B5), U75.1, U76.7 (A5), U76.13 (B5), U78.1, U79.7 (A5), U79.13 (B5), U81.1, U82.7 (A5), U82.13 (B5), U84.1, U85.7 (A5), U85.13 (B5), U87.1, U88.7 (A5), U88.13 (B5), U90.1, U91.7 (A5), U91.13 (B5), U93.1, U94.7 (A5), U94.13 (B5), U96.1, U97.7 (A5), U97.13 (B5), U99.1, U100.7 (A5), U100.13 (B5), U102.1, U103.7 (A5), U103.13 (B5), U105.1, U106.7 (A5), U106.13 (B5), U108.1, U109.7 (A5), U109.13 (B5), U111.1, U112.7 (A5), U112.13 (B5), U114.1, U115.7 (A5), U115.13 (B5), U117.1, U118.7 (A5), U118.13 (B5), U120.1, U121.7 (A5), U121.13 (B5), U123.1, U124.7 (A5), U124.13 (B5), U126.1, U127.7 (A5), U127.13 (B5), U129.1, U130.7 (A5), U130.13 (B5), U132.1, U133.7 (A5), U133.13 (B5), U135.1, U136.7 (A5), U136.13 (B5), U138.1, U139.7 (A5), U139.13 (B5), U141.1, U142.7 (A5), U142.13 (B5), U144.1, U145.7 (A5), U145.13 (B5), U147.1, U148.7 (A5), U148.13 (B5), U150.1, U151.7 (A5), U151.13 (B5), U153.1, U154.7 (A5), U154.13 (B5), U156.1, U157.7 (A5), U157.13 (B5), U159.1, U160.7 (A5), U160.13 (B5), U162.1, U163.7 (A5), U163.13 (B5), U165.1, U166.7 (A5), U166.13 (B5), U168.1, U169.7 (A5), U169.13 (B5), U171.1, U172.7 (A5), U172.13 (B5), U174.1, U175.7 (A5), U175.13 (B5), U177.1, U178.7 (A5), U178.13 (B5), U180.1, U181.7 (A5), U181.13 (B5), U183.1, U184.7 (A5), U184.13 (B5), U186.1, U187.7 (A5), U187.13 (B5), U189.1, U190.7 (A5)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
/D6: U1.8 (A6), U1.12 (B6), U3.4, U4.8 (A6), U4.12 (B6), U6.4, U7.8 (A6), U7.12 (B6), U9.4, U10.8 (A6), U10.12 (B6), U12.4, U13.8 (A6), U13.12 (B6), U15.4, U16.8 (A6), U16.12 (B6), U18.4, U19.8 (A6), U19.12 (B6), U21.4, U22.8 (A6), U22.12 (B6), U24.4, U25.8 (A6), U25.12 (B6), U27.4, U28.8 (A6), U28.12 (B6), U30.4, U31.8 (A6), U31.12 (B6), U33.4, U34.8 (A6), U34.12 (B6), U36.4, U37.8 (A6), U37.12 (B6), U39.4, U40.8 (A6), U40.12 (B6), U42.4, U43.8 (A6), U43.12 (B6), U45.4, U46.8 (A6), U46.12 (B6), U48.4, U49.8 (A6), U49.12 (B6), U51.4, U52.8 (A6), U52.12 (B6), U54.4, U55.8 (A6), U55.12 (B6), U57.4, U58.8 (A6), U58.12 (B6), U60.4, U61.8 (A6), U61.12 (B6), U63.4, U64.8 (A6), U64.12 (B6), U66.4, U67.8 (A6), U67.12 (B6), U69.4, U70.8 (A6), U70.12 (B6), U72.4, U73.8 (A6), U73.12 (B6), U75.4, U76.8 (A6), U76.12 (B6), U78.4, U79.8 (A6), U79.12 (B6), U81.4, U82.8 (A6), U82.12 (B6), U84.4, U85.8 (A6), U85.12 (B6), U87.4, U88.8 (A6), U88.12 (B6), U90.4, U91.8 (A6), U91.12 (B6), U93.4, U94.8 (A6), U94.12 (B6), U96.4, U97.8 (A6), U97.12 (B6), U99.4, U100.8 (A6), U100.12 (B6), U102.4, U103.8 (A6), U103.12 (B6), U105.4, U106.8 (A6), U106.12 (B6), U108.4, U109.8 (A6), U109.12 (B6), U111.4, U112.8 (A6), U112.12 (B6), U114.4, U115.8 (A6), U115.12 (B6), U117.4, U118.8 (A6), U118.12 (B6), U120.4, U121.8 (A6), U121.12 (B6), U123.4, U124.8 (A6), U124.12 (B6), U126.4, U127.8 (A6), U127.12 (B6), U129.4, U130.8 (A6), U130.12 (B6), U132.4, U133.8 (A6), U133.12 (B6), U135.4, U136.8 (A6), U136.12 (B6), U138.4, U139.8 (A6), U139.12 (B6), U141.4, U142.8 (A6), U142.12 (B6), U144.4, U145.8 (A6), U145.12 (B6), U147.4, U148.8 (A6), U148.12 (B6), U150.4, U151.8 (A6), U151.12 (B6), U153.4, U154.8 (A6), U154.12 (B6), U156.4, U157.8 (A6), U157.12 (B6), U159.4, U160.8 (A6), U160.12 (B6), U162.4, U163.8 (A6), U163.12 (B6), U165.4, U166.8 (A6), U166.12 (B6), U168.4, U169.8 (A6), U169.12 (B6), U171.4, U172.8 (A6), U172.12 (B6), U174.4, U175.8 (A6), U175.12 (B6), U177.4, U178.8 (A6), U178.12 (B6), U180.4, U181.8 (A6), U181.12 (B6), U183.4, U184.8 (A6), U184.12 (B6), U186.4, U187.8 (A6), U187.12 (B6), U189.4, U190.8 (A6)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
/D7: U1.9 (A7), U1.11 (B7), U3.3, U4.9 (A7), U4.11 (B7), U6.3, U7.9 (A7), U7.11 (B7), U9.3, U10.9 (A7), U10.11 (B7), U12.3, U13.9 (A7), U13.11 (B7), U15.3, U16.9 (A7), U16.11 (B7), U18.3, U19.9 (A7), U19.11 (B7), U21.3, U22.9 (A7), U22.11 (B7), U24.3, U25.9 (A7), U25.11 (B7), U27.3, U28.9 (A7), U28.11 (B7), U30.3, U31.9 (A7), U31.11 (B7), U33.3, U34.9 (A7), U34.11 (B7), U36.3, U37.9 (A7), U37.11 (B7), U39.3, U40.9 (A7), U40.11 (B7), U42.3, U43.9 (A7), U43.11 (B7), U45.3, U46.9 (A7), U46.11 (B7), U48.3, U49.9 (A7), U49.11 (B7), U51.3, U52.9 (A7), U52.11 (B7), U54.3, U55.9 (A7), U55.11 (B7), U57.3, U58.9 (A7), U58.11 (B7), U60.3, U61.9 (A7), U61.11 (B7), U63.3, U64.9 (A7), U64.11 (B7), U66.3, U67.9 (A7), U67.11 (B7), U69.3, U70.9 (A7), U70.11 (B7), U72.3, U73.9 (A7), U73.11 (B7), U75.3, U76.9 (A7), U76.11 (B7), U78.3, U79.9 (A7), U79.11 (B7), U81.3, U82.9 (A7), U82.11 (B7), U84.3, U85.9 (A7), U85.11 (B7), U87.3, U88.9 (A7), U88.11 (B7), U90.3, U91.9 (A7), U91.11 (B7), U93.3, U94.9 (A7), U94.11 (B7), U96.3, U97.9 (A7), U97.11 (B7), U99.3, U100.9 (A7), U100.11 (B7), U102.3, U103.9 (A7), U103.11 (B7), U105.3, U106.9 (A7), U106.11 (B7), U108.3, U109.9 (A7), U109.11 (B7), U111.3, U112.9 (A7), U112.11 (B7), U114.3, U115.9 (A7), U115.11 (B7), U117.3, U118.9 (A7), U118.11 (B7), U120.3, U121.9 (A7), U121.11 (B7), U123.3, U124.9 (A7), U124.11 (B7), U126.3, U127.9 (A7), U127.11 (B7), U129.3, U130.9 (A7), U130.11 (B7), U132.3, U133.9 (A7), U133.11 (B7), U135.3, U136.9 (A7), U136.11 (B7), U138.3, U139.9 (A7), U139.11 (B7), U141.3, U142.9 (A7), U142.11 (B7), U144.3, U145.9 (A7), U145.11 (B7), U147.3, U148.9 (A7), U148.11 (B7), U150.3, U151.9 (A7), U151.11 (B7), U153.3, U154.9 (A7), U154.11 (B7), U156.3, U157.9 (A7), U157.11 (B7), U159.3, U160.9 (A7), U160.11 (B7), U162.3, U163.9 (A7), U163.11 (B7), U165.3, U166.9 (A7), U166.11 (B7), U168.3, U169.9 (A7), U169.11 (B7), U171.3, U172.9 (A7), U172.11 (B7), U174.3, U175.9 (A7), U175.11 (B7), U177.3, U178.9 (A7), U178.11 (B7), U180.3, U181.9 (A7), U181.11 (B7), U183.3, U184.9 (A7), U184.11 (B7), U186.3, U187.9 (A7), U187.11 (B7), U189.3, U190.9 (A7)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
GND: C1.2, C2.2, C3.2, C4.2, C5.2, C6.2, C7.2, C8.2, C9.2, C10.2, C11.2, C12.2, C13.2, C14.2, C15.2, C16.2, C17.2, C18.2, C19.2, C20.2, C21.2, C22.2, C23.2, C24.2, C25.2, C26.2, C27.2, C28.2, C29.2, C30.2, C31.2, C32.2, C33.2, C34.2, C35.2, C36.2, C37.2, C38.2, C39.2, C40.2, C41.2, C42.2, C43.2, C44.2, C45.2, C46.2, C47.2, C48.2, C49.2, C50.2, C51.2, C52.2, C53.2, C54.2, C55.2, C56.2, C57.2, C58.2, C59.2, C60.2, C61.2, C62.2, C63.2, C64.2, C65.2, C66.2, C67.2, C68.2, C69.2, C70.2, C71.2, C72.2, C73.2, C74.2, C75.2, C76.2, C77.2, C78.2, C79.2, C80.2, C81.2, U1.10 (GND), U2.2, U3.2, U4.10 (GND), U5.2, U6.2, U7.10 (GND), U8.2, U9.2, U10.10 (GND), U11.2, U12.2, U13.10 (GND), U14.2, U15.2, U16.10 (GND), U17.2, U18.2, U19.10 (GND), U20.2, U21.2, U22.10 (GND), U23.2, U24.2, U25.10 (GND), U26.2, U27.2, U28.10 (GND), U29.2, U30.2, U31.10 (GND), U32.2, U33.2, U34.10 (GND), U35.2, U36.2, U37.10 (GND), U38.2, U39.2, U40.10 (GND), U41.2, U42.2, U43.10 (GND), U44.2, U45.2, U46.10 (GND), U47.2, U48.2, U49.10 (GND), U50.2, U51.2, U52.10 (GND), U53.2, U54.2, U55.10 (GND), U56.2, U57.2, U58.10 (GND), U59.2, U60.2, U61.10 (GND), U62.2, U63.2, U64.10 (GND), U65.2, U66.2, U67.10 (GND), U68.2, U69.2, U70.10 (GND), U71.2, U72.2, U73.10 (GND), U74.2, U75.2, U76.10 (GND), U77.2, U78.2, U79.10 (GND), U80.2, U81.2, U82.10 (GND), U83.2, U84.2, U85.10 (GND), U86.2, U87.2, U88.10 (GND), U89.2, U90.2, U91.10 (GND), U92.2, U93.2, U94.10 (GND), U95.2, U96.2, U97.10 (GND), U98.2, U99.2, U100.10 (GND), U101.2, U102.2, U103.10 (GND), U104.2, U105.2, U106.10 (GND), U107.2, U108.2, U109.10 (GND)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
unnamed: C1.1, C2.1, C3.1, C4.1, C5.1, C6.1, C7.1, C8.1, C9.1, C10.1, C11.1, C12.1, C13.1, C14.1, C15.1, C16.1, C17.1, C18.1, C19.1, C20.1, C21.1, C22.1, C23.1, C24.1, C25.1, C26.1, C27.1, C28.1, C29.1, C30.1, C31.1, C32.1, C33.1, C34.1, C35.1, C36.1, C37.1, C38.1, C39.1, C40.1, C41.1, C42.1, C43.1, C44.1, C45.1, C46.1, C47.1, C48.1, C49.1, C50.1, C51.1, C52.1, C53.1, C54.1, C55.1, C56.1, C57.1, C58.1, C59.1, C60.1, C61.1, C62.1, C63.1, C64.1, C65.1, C66.1, C67.1, C68.1, C69.1, C70.1, C71.1, C72.1, C73.1, C74.1, C75.1, C76.1, C77.1, C78.1, C79.1, C80.1, C81.1, R1.2, R2.2, R3.2, R4.2, R5.2, R6.2, R7.2, R8.2, R9.2, R10.2, R11.2, R12.2, R13.2, R14.2, R15.2, R16.2, R17.2, R18.2, R19.2, R20.2, R21.2, R22.2, R23.2, R24.2, R25.2, R26.2, R27.2, R28.2, R29.2, R30.2, R31.2, R32.2, R33.2, R34.2, R35.2, R36.2, R37.2, R38.2, R39.2, R40.2, R41.2, R42.2, R43.2, R44.2, R45.2, R46.2, R47.2, R48.2, R49.2, R50.2, R51.2, R52.2, R53.2, R54.2, R55.2, R56.2, R57.2, R58.2, R59.2, R60.2, R61.2, R62.2, R63.2, R64.2, R65.2, R66.2, R67.2, R68.2, R69.2, R70.2, R71.2, R72.2, R73.2, R74.2, R75.2, R76.2, R77.2, R78.2, R79.2, R80.2, R81.2, U2.5, U3.5, U5.5, U6.5, U8.5, U9.5, U11.5, U12.5, U14.5, U15.5, U17.5, U18.5, U20.5, U21.5, U23.5, U24.5, U26.5, U27.5, U29.5, U30.5, U32.5, U33.5, U35.5, U36.5, U38.5, U39.5, U41.5, U42.5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
VCC: R1.1, R2.1, R3.1, R4.1, R5.1, R6.1, R7.1, R8.1, R9.1, R10.1, R11.1, R12.1, R13.1, R14.1, R15.1, R16.1, R17.1, R18.1, R19.1, R20.1, R21.1, R22.1, R23.1, R24.1, R25.1, R26.1, R27.1, R28.1, R29.1, R30.1, R31.1, R32.1, R33.1, R34.1, R35.1, R36.1, R37.1, R38.1, R39.1, R40.1, R41.1, R42.1, R43.1, R44.1, R45.1, R46.1, R47.1, R48.1, R49.1, R50.1, R51.1, R52.1, R53.1, R54.1, R55.1, R56.1, R57.1, R58.1, R59.1, R60.1, R61.1, R62.1, R63.1, R64.1, R65.1, R66.1, R67.1, R68.1, R69.1, R70.1, R71.1, R72.1, R73.1, R74.1, R75.1, R76.1, R77.1, R78.1, R79.1, R80.1, R81.1, U1.20 (VCC), U4.20 (VCC), U7.20 (VCC), U10.20 (VCC), U13.20 (VCC), U16.20 (VCC), U19.20 (VCC), U22.20 (VCC), U25.20 (VCC), U28.20 (VCC), U31.20 (VCC), U34.20 (VCC), U37.20 (VCC), U40.20 (VCC), U43.20 (VCC), U46.20 (VCC), U49.20 (VCC), U52.20 (VCC), U55.20 (VCC), U58.20 (VCC), U61.20 (VCC), U64.20 (VCC), U67.20 (VCC), U70.20 (VCC), U73.20 (VCC), U76.20 (VCC), U79.20 (VCC), U82.20 (VCC), U85.20 (VCC), U88.20 (VCC), U91.20 (VCC), U94.20 (VCC), U97.20 (VCC), U100.20 (VCC), U103.20 (VCC), U106.20 (VCC), U109.20 (VCC), U112.20 (VCC), U115.20 (VCC), U118.20 (VCC), U121.20 (VCC), U124.20 (VCC), U127.20 (VCC), U130.20 (VCC), U133.20 (VCC), U136.20 (VCC), U139.20 (VCC), U142.20 (VCC), U145.20 (VCC), U148.20 (VCC), U151.20 (VCC), U154.20 (VCC), U157.20 (VCC), U160.20 (VCC), U163.20 (VCC), U166.20 (VCC), U169.20 (VCC), U172.20 (VCC), U175.20 (VCC), U178.20 (VCC), U181.20 (VCC), U184.20 (VCC), U187.20 (VCC), U190.20 (VCC), U193.20 (VCC), U196.20 (VCC), U199.20 (VCC), U202.20 (VCC), U205.20 (VCC), U208.20 (VCC), U211.20 (VCC), U214.20 (VCC), U217.20 (VCC), U220.20 (VCC), U223.20 (VCC), U226.20 (VCC), U229.20 (VCC), U232.20 (VCC), U235.20 (VCC), U238.20 (VCC), U241.20 (VCC)

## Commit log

2020-08-29 moved sub schematics to submodule repository
2020-08-29 ignore all backup directories and ibom files
2020-08-29 added source files
2020-08-29 added generated assets
2020-08-30 added picture of sandwich
2020-08-30 added links
2020-08-30 fix STM32 USB; closes #2
2020-08-30 fix upside down silkscreen; closes #3
2020-09-04 fixed wrong JTAG signal assignment on FTDI
2020-09-04 exported schematic to PDF
2020-10-30 Backlink to CADLAB.io has been added.
2022-05-04 add scripts for JLCPCB
2022-05-04 add scripts directory explanation
2022-05-17 update nixpkgs
2022-05-17 make kicad version selection easier
2022-06-16 made script compatible with lcsc
2022-06-16 added empty project
2022-06-16 add usage explanation
2022-06-16 add sed command
2022-06-16 add missing -a
2022-06-16 explicitly add source files
2022-09-22 add default text variables
2022-09-22 move renderings from assets to exports
2022-09-22 set pkgs to nixos-22.05-2022_08_27; updates kicad to 6.0.5
2022-10-03 added OSH Park boards setups; moved template
2022-10-03 adapted readme to new structure
2022-10-03 make OSH Park 2 layer default
2022-10-03 added library directory
2023-01-05 reduce file content and bump version
2023-01-30 finished version 0.2.0
2023-01-31 added connectors for v8.0; improved power layout
2023-02-08 switch P4 and R2 on HUB75 J4; closes #5
2023-02-10 add test points and leds - closes #1; add fuse - closes #4; add silk screen art
2023-02-12 add zero volt diodes to USB and modules; add status LEDs; add RP2040 SWD - closes #9
2023-02-25 moved to KiCad v7.0.0
2023-02-25 rotated v8 jtag connector - closes #10; moved aux jtag connectors and pmod wires to makes space for #14;
2023-02-25 add USON-8 footprint for W25Q16JV style flash; closes #13
2023-03-18 add prototyping area; closes #14
2023-03-19 remove old files
2023-03-19 automate export and pattern creation
2023-03-19 bump kicad to 7.0.1
2023-03-19 add missing library
2023-03-19 add hook; add automation instructions
2023-03-19 refresh renderings
2023-03-20 copy from template
2023-03-20 increase pmod labels; closes #15
2023-04-19 remade hc245t bypass panel
2023-04-19 fix file path regex
